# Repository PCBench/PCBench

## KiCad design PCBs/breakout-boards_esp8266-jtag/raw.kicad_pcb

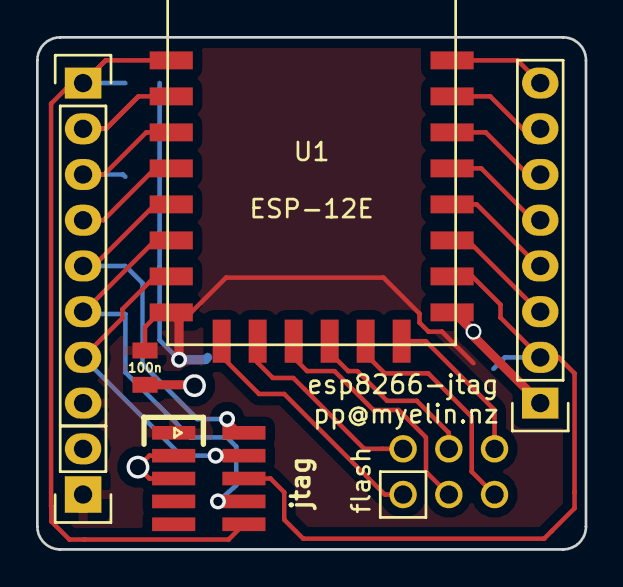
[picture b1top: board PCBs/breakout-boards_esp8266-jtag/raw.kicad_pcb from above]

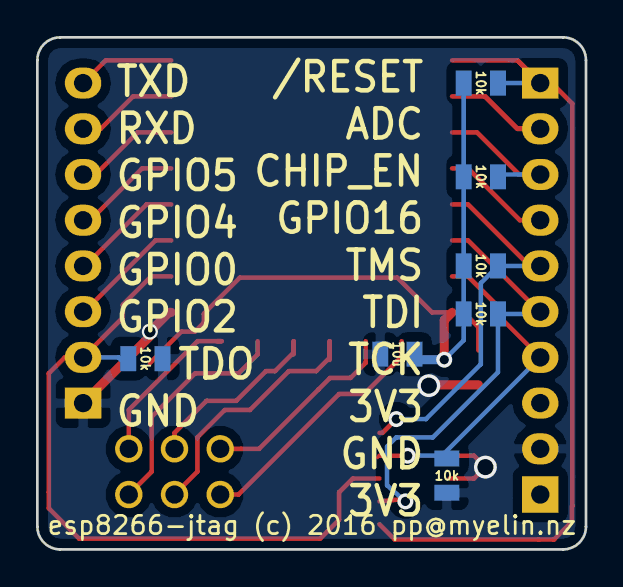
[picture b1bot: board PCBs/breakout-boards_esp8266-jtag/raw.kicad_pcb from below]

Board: 2 copper layers, 30.5 x 28.4 mm, 14 parts (7 on the bottom side), 22 nets.

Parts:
C1: 10u; C0805_nosilkscreen
C2: 100n; C0805_nosilkscreen
CON1: jtag; pin_array_5x2_50mil_smd
P1, P3: CONN_01X08; Pin_Header_Straight_1x08
P2: flash; pin_array_2x3_100mil_pth
P4: CONN_01X02; Pin_Header_Straight_1x02
R1, R2, R3, R4, R5, R6: 10k; R0805_nosilkscreen
U1: ESP-12E; ESP8266-ESP-12E

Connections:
/3v3: C1.1, C2.1, CON1.1, P1.8, P4.1, R1.2, R2.2, R4.1, R5.1, U1.8
/adc: P1.2, U1.2
/chip_en: P1.3, R2.1, U1.3
/cs0: P2.1, U1.9
/gnd: C1.2, C2.2, CON1.3, CON1.5, P3.1, P4.2, R3.1, R6.1, U1.15
/gpio0: P3.4, U1.18
/gpio2: P3.3, U1.17
/gpio4: P3.5, U1.19
/gpio5: P3.6, U1.20
/gpio9: P2.3, U1.11
/gpio10: P2.4, U1.12
/gpio16: P1.4, U1.4
/miso: P2.2, U1.10
/mosi: P2.5, U1.13
/nreset: CON1.10, P1.1, R1.1, U1.1
/sclk: P2.6, U1.14
/tck: CON1.4, P1.7, R6.2, U1.7
/tdi: CON1.8, P1.6, R5.2, U1.6
/tdo: CON1.6, P3.2, R3.2, U1.16
/tms: CON1.2, P1.5, R4.2, U1.5
/u0rxd: P3.7, U1.21
/u0txd: P3.8, U1.22

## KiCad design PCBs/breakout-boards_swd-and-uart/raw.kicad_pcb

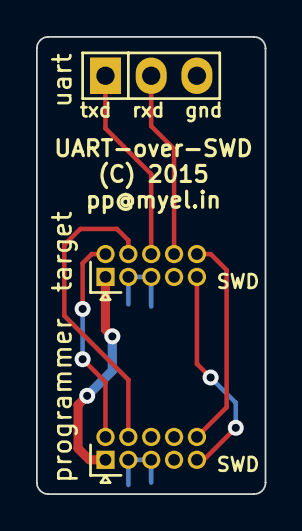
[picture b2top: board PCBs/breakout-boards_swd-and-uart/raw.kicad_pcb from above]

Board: 2 copper layers, 12.7 x 25.4 mm, 3 parts (0 on the bottom side), 8 nets.

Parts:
P1: target; pin_array_5x2_50mil
P2: uart; Socket_Strip_Straight_1x03
P3: programmer; pin_array_5x2_50mil

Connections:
/GND: P1.3, P1.5, P2.3, P3.3, P3.5
/GND_DET: P1.9, P3.9
/RXD: P1.8, P2.2
/SWCLK: P1.4, P3.4
/SWDIO: P1.2, P3.2
/TXD: P1.6, P2.1
/VCC: P1.1, P3.1
/nRESET: P1.10, P3.10

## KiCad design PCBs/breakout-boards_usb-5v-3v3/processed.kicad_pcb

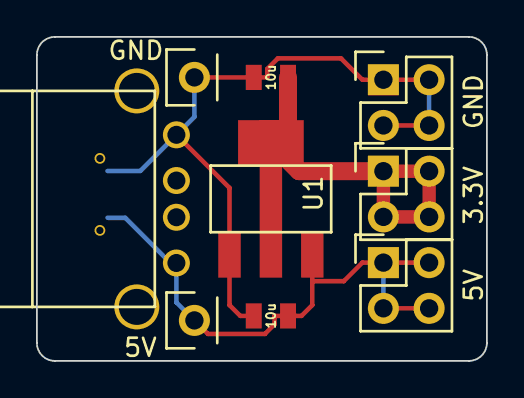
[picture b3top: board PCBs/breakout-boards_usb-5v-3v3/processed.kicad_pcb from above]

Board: 2 copper layers, 25.0 x 18.0 mm, 10 parts (1 on the bottom side), 3 nets.

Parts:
C1, C2: 10u; SM0805_NOSILKSCREEN
CON1: usb_plug; USB_A_THRU_HOLE
CON2: micro_usb_socket; micro_usb_b_smd_bottom_mount
P1: 5V; Socket_Strip_Straight_2x02
P2: 3.3V; Socket_Strip_Straight_2x02
P3: GND; Socket_Strip_Straight_2x02
P4: 5V; Socket_Strip_Straight_1x01
P5: GND; Socket_Strip_Straight_1x01
U1: NCP1117ST33T3G; SOT-223-LDO-1117LV

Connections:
/3v3: C2.1, P2.1, P2.2, P2.3, P2.4, U1.2
/gnd: C1.2, C2.2, CON1.4, CON2.5, P3.1, P3.2, P3.3, P3.4, P5.1, U1.1
/vbus: C1.1, CON1.1, CON2.1, P1.1, P1.2, P1.3, P1.4, P4.1, U1.3

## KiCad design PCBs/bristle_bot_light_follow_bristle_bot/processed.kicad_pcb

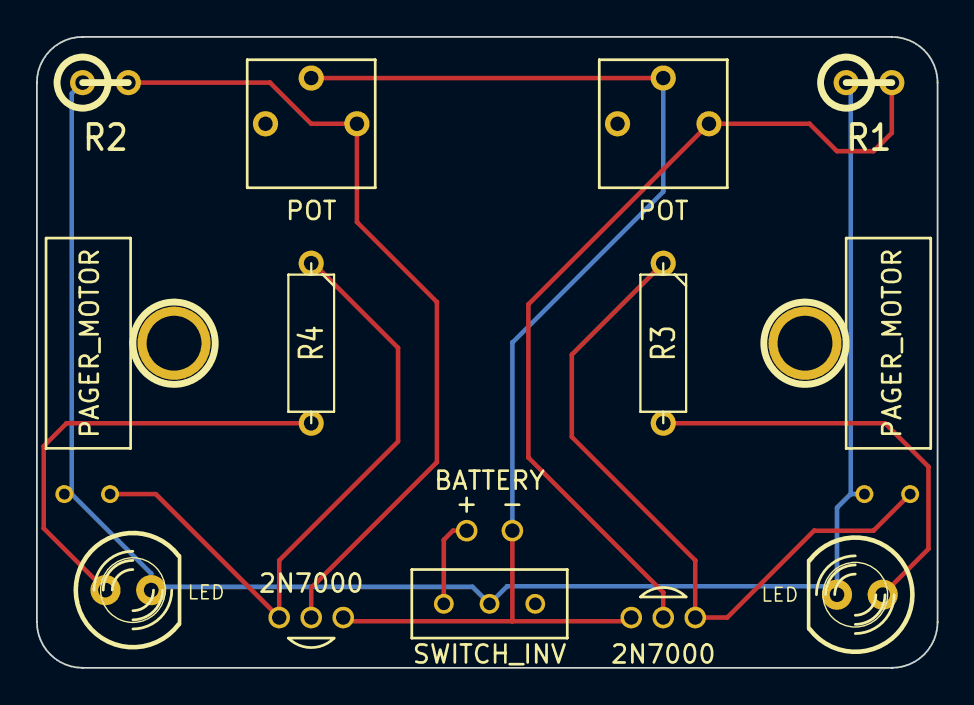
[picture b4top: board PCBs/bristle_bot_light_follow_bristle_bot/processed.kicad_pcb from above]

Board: 2 copper layers, 50.0 x 35.1 mm, 17 parts (0 on the bottom side), 9 nets.

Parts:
1PIN, 1PIN_2: P***; 1pin
BT1: BATTERY; battery_custom
D1, D2: LED; LED-5MM
M1, M2: PAGER_MOTOR; pager_motor_custom
Q1, Q2: 2N7000
R1, R2: R; R1
R3, R4: R; R3-5
RV1, RV2: POT; pot_custom
SW1: SWITCH_INV; switch_small_custom
VAL: OSH_final_silks_back

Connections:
GND: BT1.2, Q1.1, Q2.1, RV1.2, RV2.2
unnamed: Q2.2, R2.2, RV2.3
unnamed: M2.2, Q2.3, R4.1
unnamed: D2.1, R4.2
unnamed: D1.1, R3.2
unnamed: M1.2, Q1.3, R3.1
unnamed: Q1.2, R1.2, RV1.3
unnamed: BT1.1, SW1.1
VCC: D1.2, D2.2, M1.1, M2.1, R1.1, R2.1, SW1.2

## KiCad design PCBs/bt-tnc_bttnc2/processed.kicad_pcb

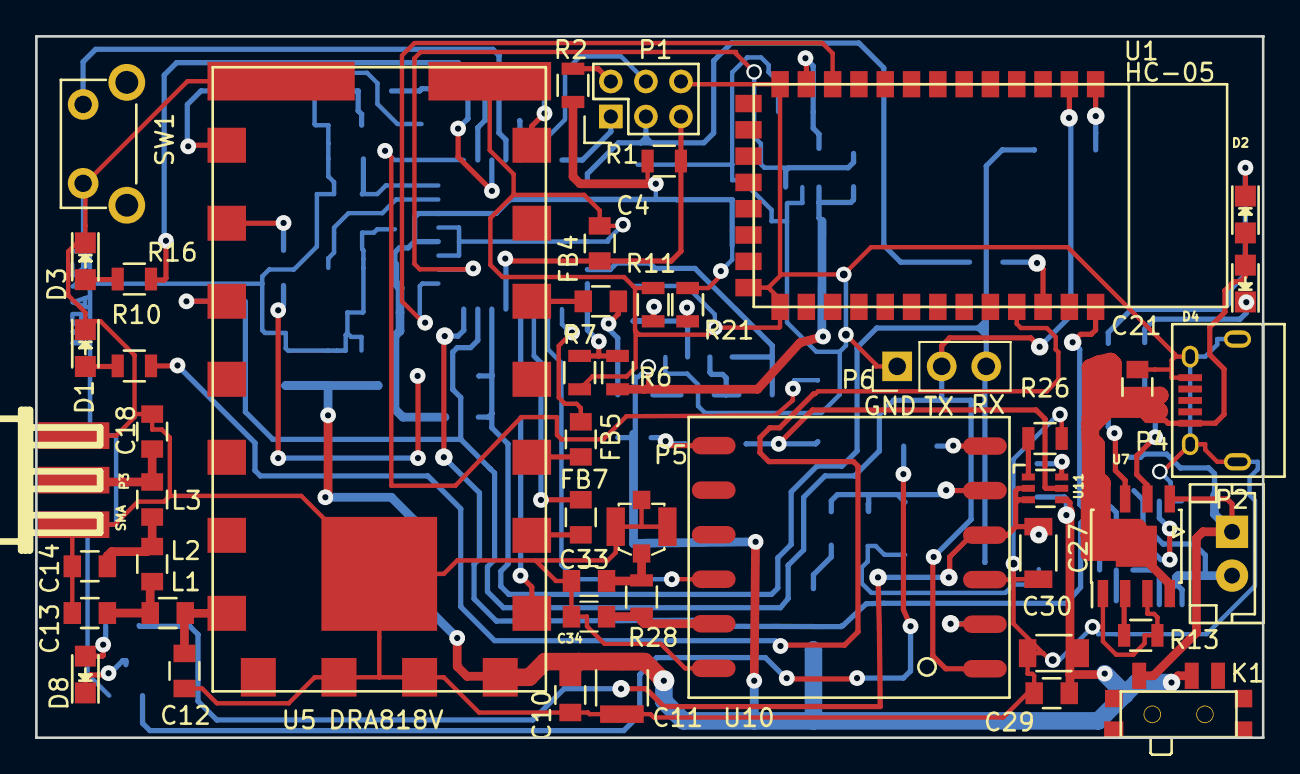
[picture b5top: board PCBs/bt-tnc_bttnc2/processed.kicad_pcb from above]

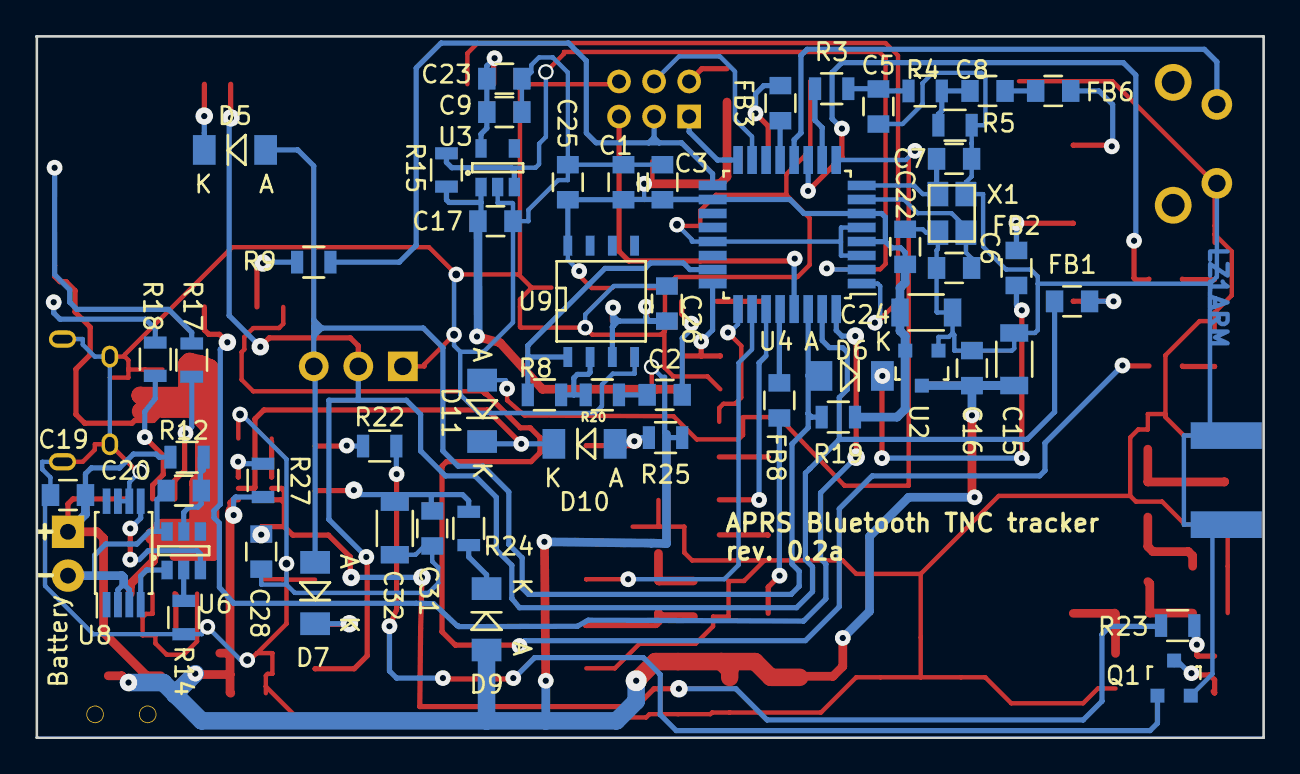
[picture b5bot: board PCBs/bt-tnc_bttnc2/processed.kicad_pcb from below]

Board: 2 copper layers, 70.0 x 40.0 mm, 105 parts (57 on the bottom side), 78 nets.

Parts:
C1, C2, C3, C4, C8, C9, C10, C16, C17, C19, C20, C21, C22, C23, C25, C26, C28, C29, C31: 100nF; C_0805
C5: 10nF; C_0805
C6, C7: 10pF; C_0805
C11: 100uF; C_1210
C12, C18: 20pF; C_0805
C13, C14: 36pF; C_0805
C15, C24, C27, C30, C32: 10uF; C_1206
C33, C34: DNI; C_0805
D1, D8: Blue LED; LED_0805
D2: Red LED; LED_0805
D3, D4: Green LED; LED_0805
D5, D7, D9, D10, D11: BAT42; MiniMELF_Standard
D6: DNI; MiniMELF_Standard
FB1, FB3, FB4, FB5, FB6, FB7, FB8: BLM21PG331SN1D; C_0805
FB2: DNI; C_0805
K1: MK12C02
L1, L3: 56nH; C_0805
L2: 68nH; C_0805
P1: ISP; Pin_Header_Straight_2x03_Pitch2.00mm
P2: BATTERY; JST_EH_B02B-EH-A_02x2.50mm_Straight
P3: SMA; CON-SMA-EDGE
P4: USB_OTG; USB_Micro-B
P5: U.FL; U.FL-Coax
P6: Serial; Pin_Header_Straight_1x03_Pitch2.54mm
Q1: MMBT3904; SOT-23
R1, R15, R19, R22, R25: 10k; R_0805
R2, R9, R27: DNI; R_0805
R3: 8k2; R_0805
R4, R8, R11, R20, R21: 100k; R_0805
R5: 15k; R_0805
R6, R7: 1M; R_0805
R10, R14, R16, R17, R18, R23, R24: 1k; R_0805
R12: 100; R_0805
R13: 1.2k; R_0805
R26, R28: 0; R_0805
SW1: SW_PUSH; SW_Tactile_SPST_Angled
U1: HC-05
U2: APE8800N; SOT-23
U3: BU33TD3WG; SOT-23-5
U4: ATMEGA328P-AU; TQFP-32_7x7mm_Pitch0.8mm
U5: DRA818V; Dorji_DRA818
U6: DW01-P; SOT-23-6
U7: TP4056; SOIC-8-1EP_3.9x4.9mm_Pitch1.27mm
U8: 8205A; TSSOP-8_4.4x3mm_Pitch0.65mm
U9: LM358; SOIC-8-N
U10: Quectel-L80; Qectel-L80
U11: FDG6342L; SC-70-6
X1: QKT-3225SMD 16.0000MHz; crystal_FA238-TSX3225

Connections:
3V3: C9.1, C23.1, U1.12, U3.5
+BATT: C10.1, C11.1, C15.1, C16.1, C17.1, C29.1, C30.1, D9.2, K1.2, R6.1, R15.2, R25.1, R27.2, U2.3, U3.1, U5.8, U11.4
DPTT: FB5.1, U4.25
ENABLE: R15.1, U3.3, U4.2
GND: C1.2, C3.1, C4.2, C5.2, C6.2, C7.2, C9.2, C10.2, C11.2, C12.2, C13.2, C14.2, C15.2, C16.2, C17.2, C18.2, C19.2, C21.2, C22.2, C23.2, C24.2, C25.2, C26.1, C27.2, C28.2, C29.2, C30.2, C31.1, C32.2, C33.2, C34.2, D1.1, D3.1, P1.6, P3.2, P4.5, P4.6, P5.2, P6.1, Q1.2, R5.1, R7.2, R11.1, R13.1, R14.2, R26.2, SW1.1, U1.13, U1.21, U1.22, U2.1, U3.2, U4.3, U4.5, U4.21, U5.9, U5.10, U7.1, U7.3, U8.6, U8.7, U9.4, U10.3, U10.12, X1.3
GPS_EN: D11.2, U4.9
GPS_RESET: U4.26, U10.10
MIC: C8.2, FB6.1
MISO: P1.1, U4.16
MOSI: P1.4, U4.15
unnamed: C2.1, R20.1
unnamed: C2.2, FB4.1
unnamed: C5.1, R3.2, R4.2
unnamed: C6.1, U4.7, X1.2
unnamed: C7.1, U4.8, X1.1
unnamed: C8.1, R4.1, R5.2
unnamed: C12.1, L1.1, U5.12
unnamed: C13.1, L1.2, L2.1
unnamed: C14.1, L2.2, L3.1
unnamed: C18.1, L3.2, P3.1
unnamed: C19.1, K1.1, P2.1, R12.2, U7.5
unnamed: C20.1, R12.1, U6.5
unnamed: C20.2, P2.2, U6.6, U8.2, U8.3
unnamed: C21.1, D2.2, D4.2, P4.1, U7.4, U7.8, U7.9
unnamed: C26.2, R11.2, R21.2, U9.3
unnamed: C27.1, C28.1, R23.1, U10.4, U11.2, U11.3
unnamed: C31.2, C32.1, R24.2, U10.5
unnamed: C33.1, P5.1, R28.2
unnamed: C34.1, R28.1, U10.11
unnamed: D1.2, R10.2
unnamed: D2.1, R17.1
unnamed: D3.2, R16.2
unnamed: D4.1, R18.2
unnamed: D5.1, U1.1
unnamed: D6.1, FB2.1
unnamed: D7.1, U10.2
unnamed: D8.1, Q1.3
unnamed: D8.2, R23.2
unnamed: D9.1, R24.1
unnamed: D10.1, D11.1, U11.5
unnamed: D10.2, R25.2, U10.7
unnamed: FB1.2, U5.16
unnamed: FB2.2, U5.17
unnamed: FB3.2, U5.1
unnamed: FB4.2, U5.3
unnamed: FB5.2, U5.5
unnamed: FB6.2, U5.18
unnamed: FB7.2, U5.6
unnamed: FB8.2, U5.7
unnamed: P1.2, R2.1
unnamed: Q1.1, R22.1
unnamed: R3.1, U4.10
unnamed: R9.2, U1.32
unnamed: R10.1, U1.31
unnamed: R13.2, U7.2
unnamed: R14.1, U6.2
unnamed: R16.1, U4.11
unnamed: R17.2, U7.6
unnamed: R18.1, U7.7
unnamed: R8.1, R20.2, U9.2
unnamed: R22.2, U10.6
unnamed: R26.1, U11.1
unnamed: R27.1, U11.6
unnamed: SW1.2, U4.12
unnamed: U1.11, U4.1
unnamed: U1.34, U4.32
unnamed: U6.1, U8.4
unnamed: U6.3, U8.5
PWR: R6.2, R7.1, U4.24
RESET: C4.1, P1.5, R1.2, U4.29
RF_H_L: FB8.1, U4.28
RF_PD: FB7.1, U4.27
RF_SQ: FB3.1, U4.13
RXD: D5.2, D6.2, D7.2, P6.3, R19.2, U4.30
SCK: P1.3, R9.1, U4.17
SPK: R8.2, U4.23, U9.1
TXD: FB1.1, P6.2, U1.2, U4.31, U10.1
VCC: C1.1, C3.2, C22.1, C24.1, C25.1, R1.1, R2.2, R19.1, R21.1, U2.2, U4.4, U4.6, U4.18, U9.8

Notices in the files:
PCBs/breakout-boards_esp8266-jtag/raw.kicad_pcb:
esp8266-jtag (c) 2016 pp@myelin.nz
PCBs/breakout-boards_swd-and-uart/raw.kicad_pcb:
(C) 2015
